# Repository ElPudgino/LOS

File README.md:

# Система мониторинга аэрационной ЛОС

Проект направлен на создание прототипа системы мониторинга аэрационной станции биологической очистки сточных вод для загородного дома. Система должна контролировать поток воды в эрлифтах и давление в воздухных магистралях, передавать показания из станции в дом по радиоканалу, сохранять историю и заранее предупреждать о неполадках.

Главная задача — обнаруживать засоры эрлифтов, снижение производительности компрессоров и нарушение режимов работы до переполнения камер и ухудшения качества очистки. Проектная цель предусматривает автономный влагозащищённый измерительный блок в станции и домашний блок приёма, хранения и анализа данных.

Основное описание целей, требований и существующих аналогов: [scs-project-docs/project.md](scs-project-docs/project.md) и [PDF](scs-project-docs/project.pdf).

## Репозитории

### Документация

| Репозиторий | Назначение |
| --- | --- |
| [scs-project-docs](scs-project-docs/) | Цели и требования проекта, описание системы, обзор аналогов, схемы и проектное предложение. |
| [scs-docs](scs-docs/) | Справочные материалы: документация на микросхемы, датчики и модули, распиновки и другие технические материалы. |

### Прошивки и программное обеспечение

| Репозиторий | Назначение |
| --- | --- |
| [scs-ch32v003-sensor](scs-ch32v003-sensor/) | Bare-metal прошивка CH32V003 для ёмкостного датчика воды в эрлифте: RC-измерения, оценка изменчивости сигнала, энергосбережение и UART. |
| [scs-transmitter-fw-v1](scs-transmitter-fw-v1/) | Прошивка передатчика на Arduino Nano и CC1101: опрос трёх датчиков по UART, проверка CRC и передача измерений и ошибок по радиоканалу. |
| [scs-receiver-fw-v1](scs-receiver-fw-v1/) | Прошивка домашнего приёмника на Arduino Nano и CC1101: приём радиопакетов и выдача телеметрии на компьютер через USB-UART. |
| [scs-frontend](scs-frontend/) | Локальный сервис на Python/FastAPI и веб-интерфейс для сбора телеметрии, хранения истории в SQLite, графиков, статистики и диагностики. |
| [scs-air-valve-arduino](scs-air-valve-arduino/) | Прошивка контроллера воздушного клапана модели септика: управление сервоприводом по состоянию поплавкового датчика. |

### Платы, конструкции и стендовое оборудование

| Репозиторий | Назначение |
| --- | --- |
| [scs-water-sensor-ch32v003](scs-water-sensor-ch32v003/) | Схема и гибкая печатная плата ёмкостного датчика на CH32V003J4M6 с измерительной RC-цепью и интерфейсом UART/SWIO. |
| [scs-transmitter-pcb-v1](scs-transmitter-pcb-v1/) | Плата передатчика: Arduino Nano, CC1101, согласование уровней и подключение трёх датчиков. |
| [scs-receiver-pcb-v1](scs-receiver-pcb-v1/) | Плата приёмника: Arduino Nano, CC1101 и согласователь логических уровней. |
| [scs-air-valve-pcb](scs-air-valve-pcb/) | Плата контроллера воздушного клапана на Arduino Nano с подключением сервопривода, поплавка и питания. |
| [scs-stand-ps](scs-stand-ps/) | Изолированный трансформаторный блок питания стенда: схема, печатная плата и файлы для её изготовления. |
| [scs-3d-models](scs-3d-models/) | Корпуса, крепления и механические узлы датчиков и стенда; исходные 3D-модели и файлы для печати. |

### Инструменты разработки

| Репозиторий | Назначение |
| --- | --- |
| [scs-arduino-ch32v003-swio](scs-arduino-ch32v003-swio/) | Варианты адаптера UART–SWIO на ATmega328P для прошивки и отладки CH32V003 через minichlink. |
| [minichlink](minichlink/) | Сторонний инструмент для прошивки и отладки CH32V003 через WCH-LinkE, включая GDB-сервер и поддержку Ardulink. |
| [arduino-offline](arduino-offline/) | Локальный набор Arduino CLI, Arduino AVR Core и компилятора для автономной сборки Arduino-прошивок. |

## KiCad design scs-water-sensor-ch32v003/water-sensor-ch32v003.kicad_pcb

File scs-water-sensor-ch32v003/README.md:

# Схема и плата для датчика потока воды

Датчик построен на базе микроконтроллера CH32V003. Прошивка в папке ../../software/ch32v003-sensor.

Печатная плата выполнена на гибкой полиимидной основе толщиной 0.1мм.

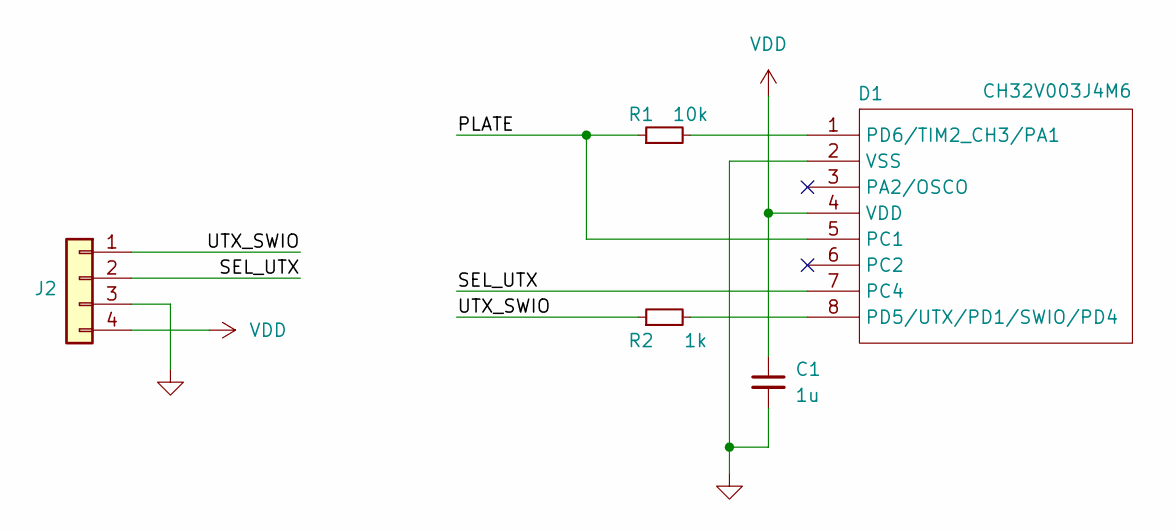
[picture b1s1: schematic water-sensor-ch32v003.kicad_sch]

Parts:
C1: 1u; C_0805_2012Metric_Pad1.18x1.45mm_HandSolder
D1: CH32V003J4M6; SOIC-8_3.9x4.9mm_P1.27mm
J2: Conn_01x04; CONN4
R1: 10k; R_0805_2012Metric_Pad1.20x1.40mm_HandSolder
R2: 1k; R_0805_2012Metric_Pad1.20x1.40mm_HandSolder

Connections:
/PLATE: D1.5 (PC1), R1.1
/SEL_UTX: D1.7 (PC4), J2.2
/UTX_SWIO: J2.1, R2.1
GND: C1.2, D1.2 (VSS), J2.3
unnamed: D1.8 (PD5/UTX/PD1/SWIO/PD4), R2.2
unnamed: D1.1 (PD6/TIM2_CH3/PA1), R1.2
VDD: C1.1, D1.4 (VDD), J2.4

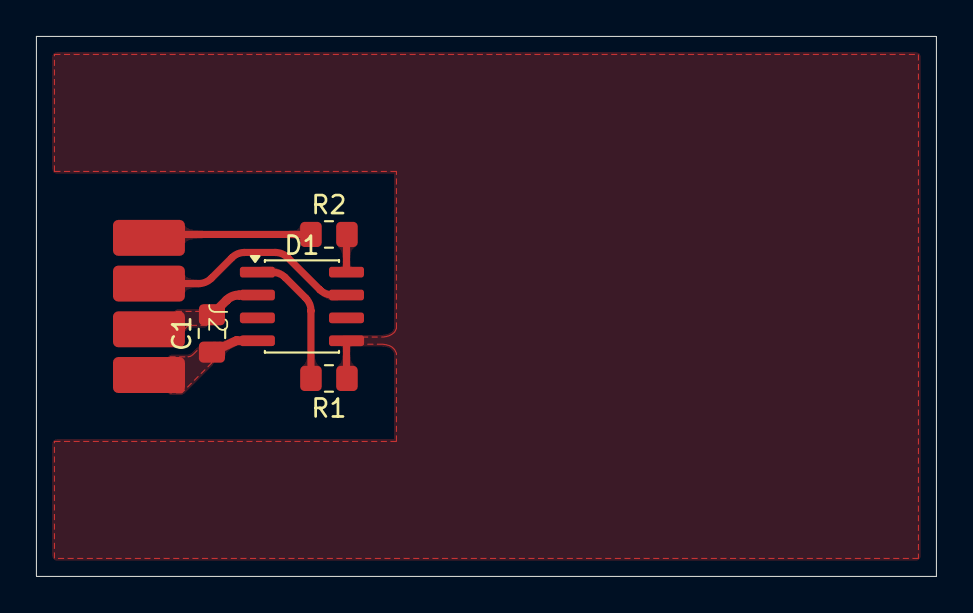
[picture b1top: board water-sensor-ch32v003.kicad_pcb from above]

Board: 2 copper layers, 50.0 x 30.0 mm, 5 parts (0 on the bottom side), 7 nets.

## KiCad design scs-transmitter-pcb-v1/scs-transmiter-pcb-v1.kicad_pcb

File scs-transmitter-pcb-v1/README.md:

# Печатная плата передатчика телеметрии

Плата измерительного блока системы мониторинга на Arduino Nano и радиомодуле CC1101. Предусмотрены согласование логических уровней, подключение трёх датчиков, транзисторные цепи запросов и объединение их линий UART TX.

Проект выполнен в KiCad и предназначен для работы с прошивкой [scs-transmitter-fw-v1](../scs-transmitter-fw-v1/).

- [scs-transmiter-pcb-v1.pdf](scs-transmiter-pcb-v1.pdf) — принципиальная схема в PDF.
- `scs-transmiter-pcb-v1.kicad_sch` и `scs-transmiter-pcb-v1.kicad_pcb` — схема и топология платы.
- `gerber/` — Gerber-файлы и сверловка для изготовления.
- `cnc/` — конфигурация и файлы для фрезеровки платы.

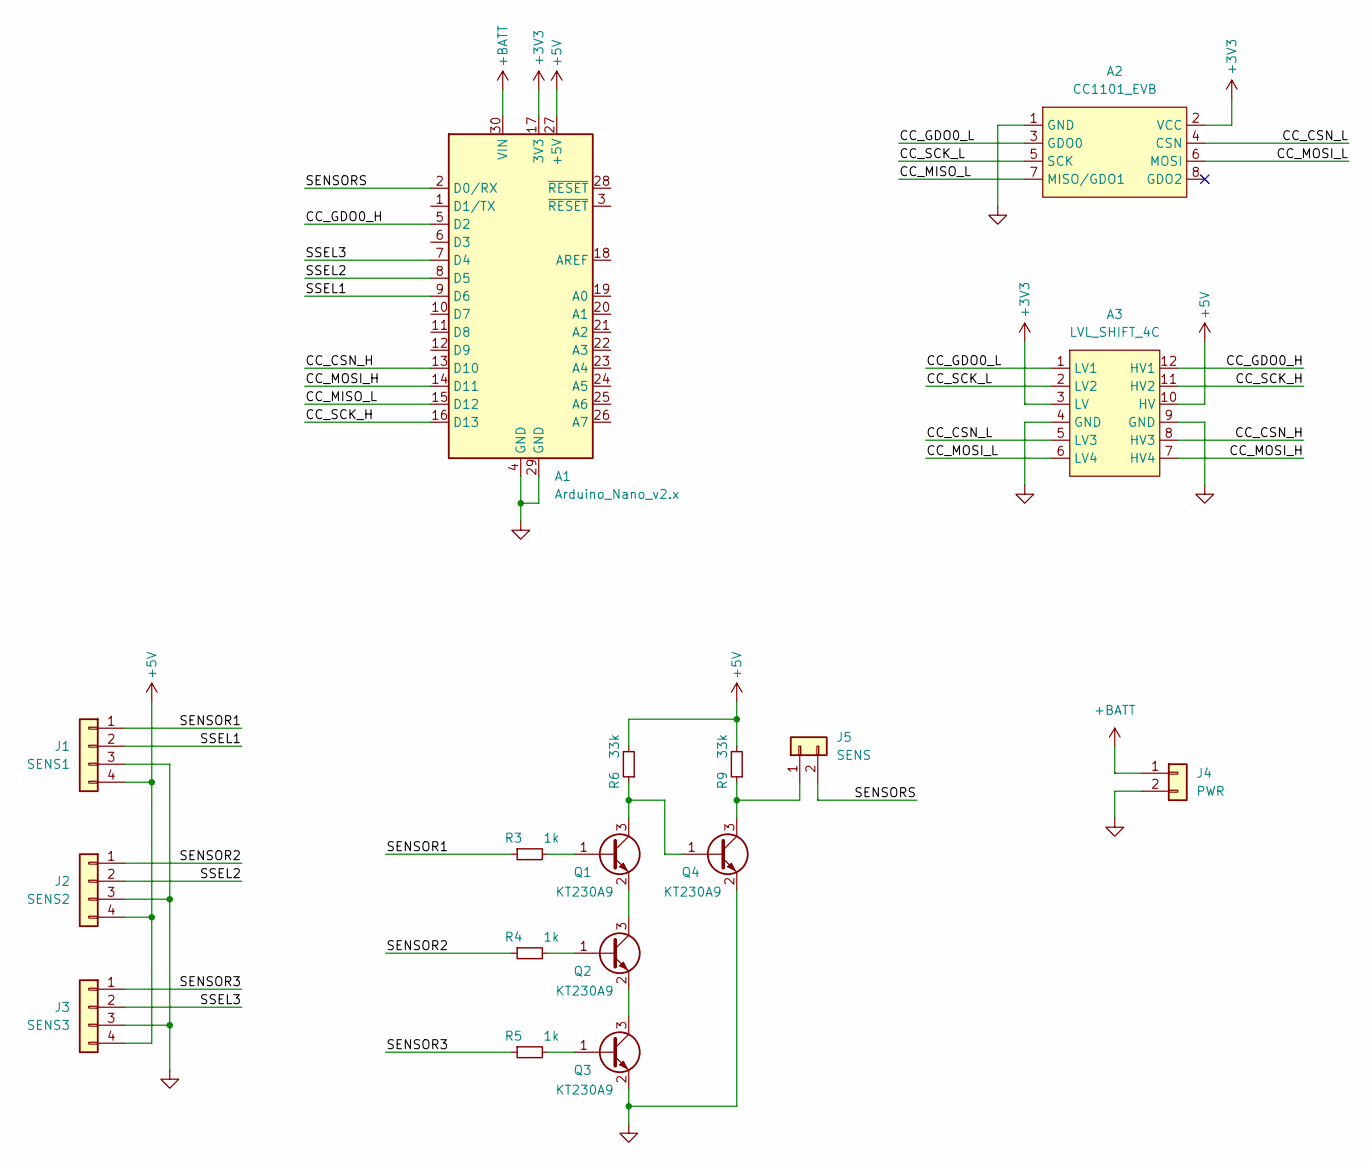
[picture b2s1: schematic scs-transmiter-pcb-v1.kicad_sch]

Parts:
A1: Arduino_Nano_v2.x; Arduino_Nano
A2: CC1101_EVB
A3: LVL_SHIFT_4C
J1: SENS1; PinHeader_1x04_P2.54mm_Vertical
J2: SENS2; PinHeader_1x04_P2.54mm_Vertical
J3: SENS3; PinHeader_1x04_P2.54mm_Vertical
J4: PWR; PinHeader_1x02_P2.54mm_Vertical
J5: SENS; PinHeader_1x02_P2.54mm_Vertical
Q1, Q2, Q3, Q4: КТ230А9; SOT-23
R3, R4, R5: 1k; R_0805_2012Metric_Pad1.20x1.40mm_HandSolder
R6, R9: 33k; R_0805_2012Metric_Pad1.20x1.40mm_HandSolder

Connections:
+3V3: A1.17 (3V3), A2.2 (VCC), A3.3 (LV)
+5V: A1.27 (+5V), A3.10 (HV), J1.4, J2.4, J3.4, R6.2, R9.2
+BATT: A1.30 (VIN), J4.1
/CC_CSN_H: A1.13 (D10), A3.8 (HV3)
/CC_CSN_L: A2.4 (CSN), A3.5 (LV3)
/CC_GDO0_H: A1.5 (D2), A3.12 (HV1)
/CC_GDO0_L: A2.3 (GDO0), A3.1 (LV1)
/CC_MISO_L: A1.15 (D12), A2.7 (MISO/GDO1)
/CC_MOSI_H: A1.14 (D11), A3.7 (HV4)
/CC_MOSI_L: A2.6 (MOSI), A3.6 (LV4)
/CC_SCK_H: A1.16 (D13), A3.11 (HV2)
/CC_SCK_L: A2.5 (SCK), A3.2 (LV2)
/SENSOR1: J1.1, R3.1
/SENSOR2: J2.1, R4.1
/SENSOR3: J3.1, R5.1
/SENSORS: A1.2 (D0/RX), J5.2
/SSEL1: A1.9 (D6), J1.2
/SSEL2: A1.8 (D5), J2.2
/SSEL3: A1.7 (D4), J3.2
GND: A1.4 (GND), A1.29 (GND), A2.1 (GND), A3.4 (GND), A3.9 (GND), J1.3, J2.3, J3.3, J4.2, Q3.2 (E), Q4.2 (E)
unnamed: J5.1, Q4.3 (C), R9.1
unnamed: Q1.1 (B), R3.2
unnamed: Q1.3 (C), Q4.1 (B), R6.1
unnamed: Q1.2 (E), Q2.3 (C)
unnamed: Q2.1 (B), R4.2
unnamed: Q2.2 (E), Q3.3 (C)
unnamed: Q3.1 (B), R5.2

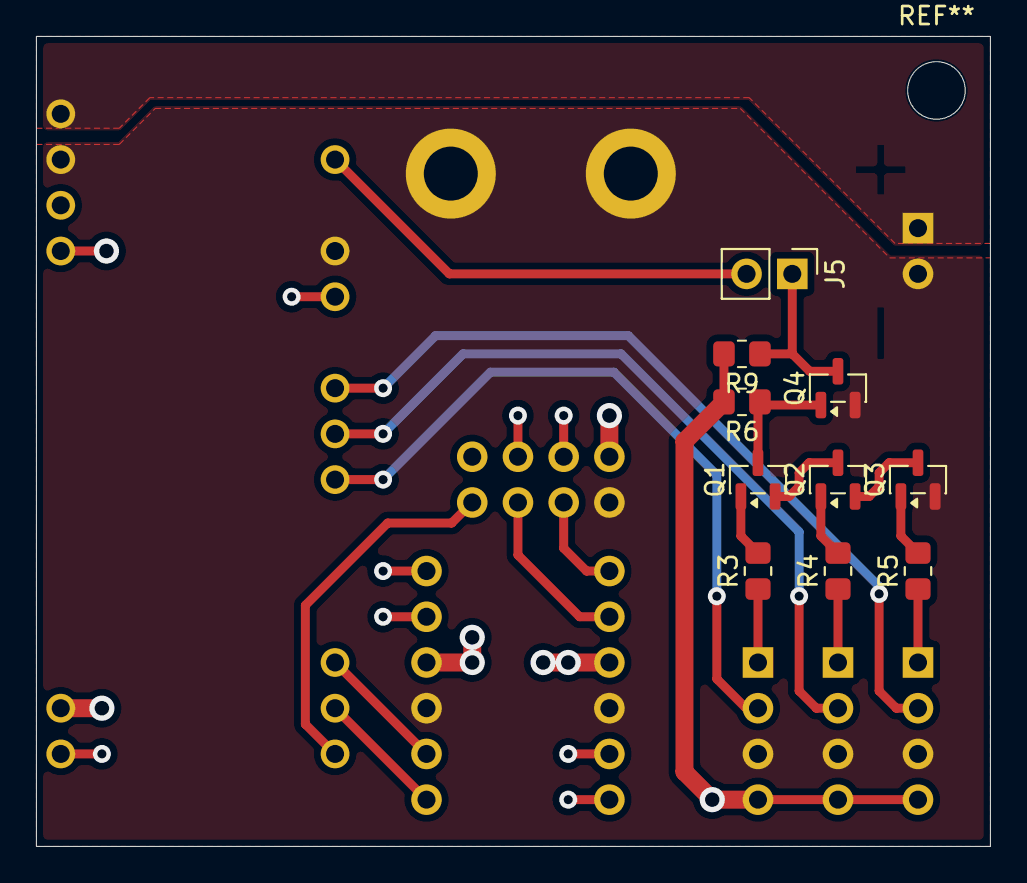
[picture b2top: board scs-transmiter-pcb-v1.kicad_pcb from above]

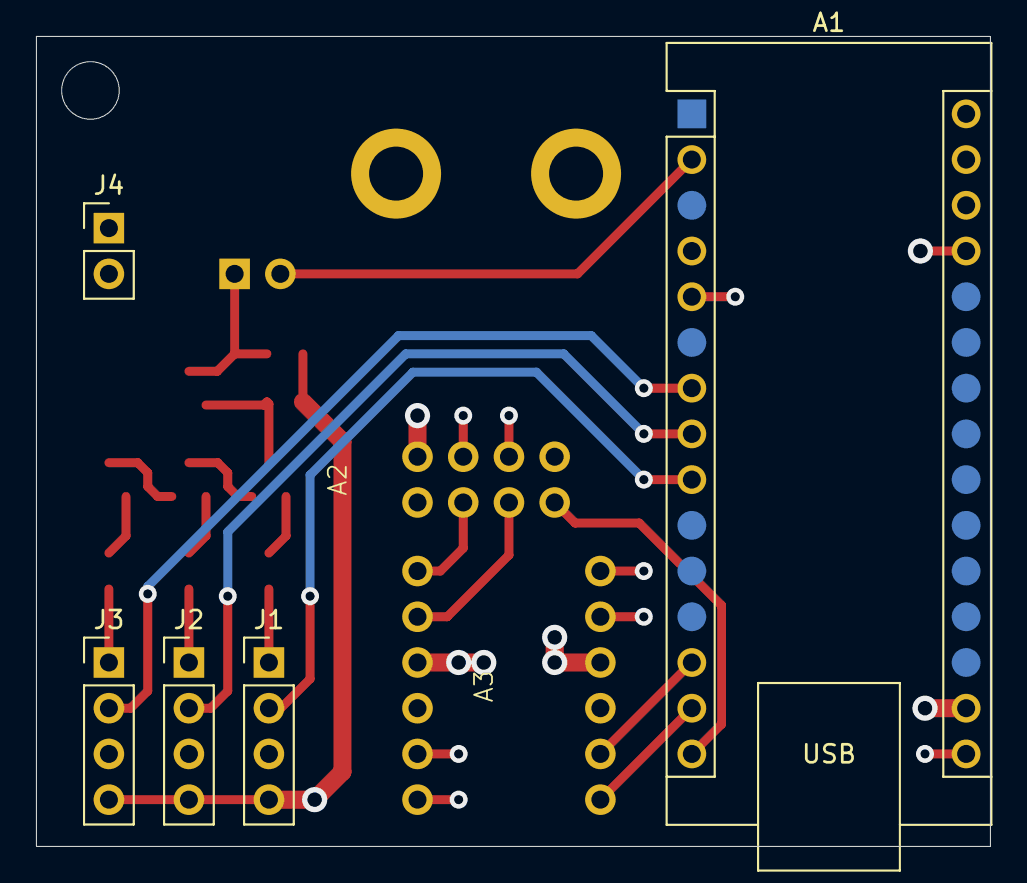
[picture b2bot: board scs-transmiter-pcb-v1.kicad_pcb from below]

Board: 2 copper layers, 53.0 x 45.0 mm, 17 parts (7 on the bottom side), 27 nets.

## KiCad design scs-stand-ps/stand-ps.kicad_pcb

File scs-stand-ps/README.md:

# Трансформаторный источник питания для стенда

Для обеспечения электробезопасности все электрические элементы стенда запитываются от изолированного трансформаторного БП. В этой папке проект печатной платы БП. Плата изготавливалась на станке ЧПУ, конфиг для `pcb2gcode` находится в папке `mill`.

Основа - трансформатор ТП-1201 с номинальным напряжением на вторичной обмотке 6В.

Схема в файле [stand-ps.pdf](stand-ps.pdf).

Форма выходного напряжения при нагрузке 1А:

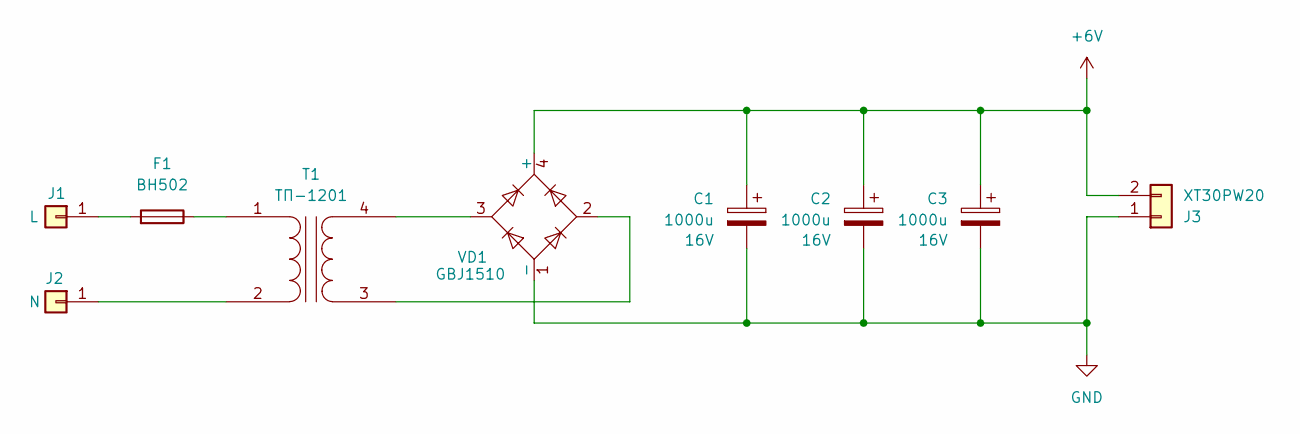
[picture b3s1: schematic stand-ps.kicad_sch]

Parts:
C1, C2, C3: 1000u; C_Radial_D10.0mm_H16.0mm_P5.00mm; Voltage 16V
F1: BH502
J1: L; TH3
J2: N; TH3
J3: XT30PW20; AMASS_XT30PW-M_1x02_P2.50mm_Horizontal
T1: ТП-1201; TP-1201
VD1: GBJ1510; Diode_Bridge_32.0x5.6x17.0mm_P10.0mm_P7.5mm

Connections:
+6V: C1.1, C2.1, C3.1, J3.2, VD1.4 (+)
GND: C1.2, C2.2, C3.2, J3.1, VD1.1 (-)
unnamed: F1.2, J1.1 (Pin_1_1)
unnamed: J2.1 (Pin_1_1), T1.2 (AB)
unnamed: F1.1, T1.1 (AA)
unnamed: T1.3 (SA), VD1.2
unnamed: T1.4 (SB), VD1.3

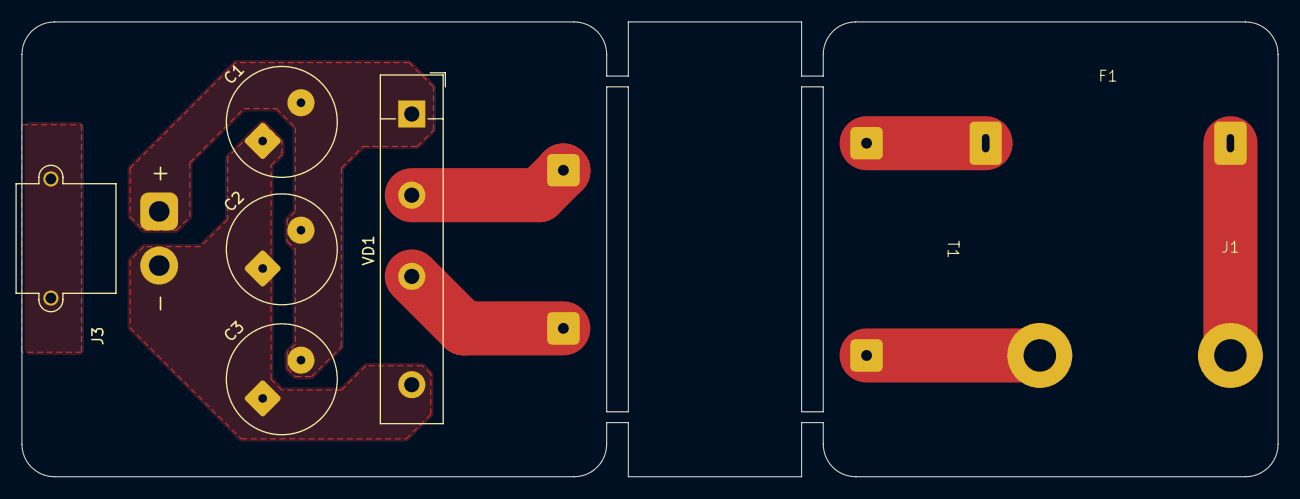
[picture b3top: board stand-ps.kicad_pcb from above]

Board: 2 copper layers, 116.0 x 42.0 mm, 9 parts (0 on the bottom side), 7 nets.

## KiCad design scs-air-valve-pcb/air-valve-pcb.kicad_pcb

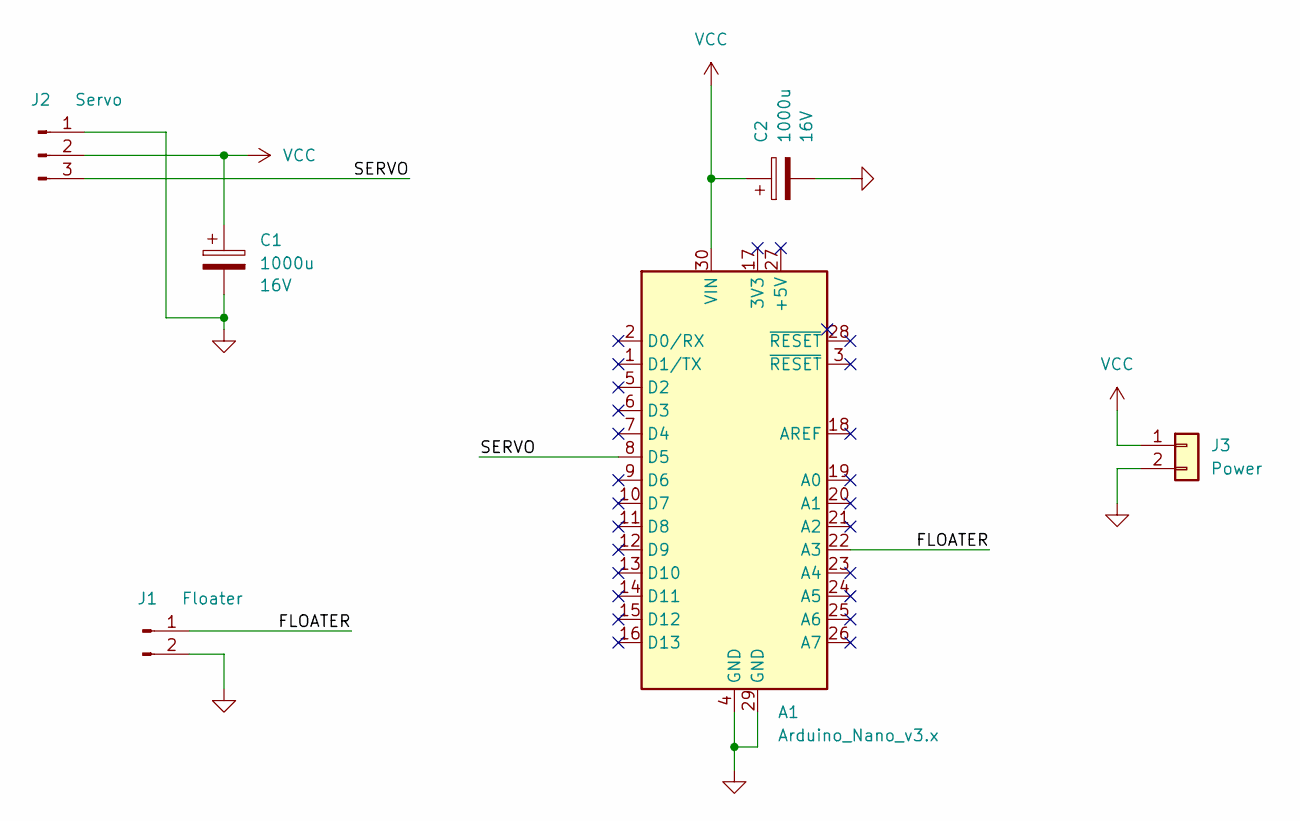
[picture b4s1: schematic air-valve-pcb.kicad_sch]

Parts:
A1: Arduino_Nano_v3.x; Arduino_Nano
C1, C2: 1000u; C_Radial_D10.0mm_H16.0mm_P5.00mm; Voltage 16V
J1: Floater; PinHeader_1x02_P2.54mm_Vertical
J2: Servo; PinHeader_1x03_P2.54mm_Vertical
J3: Power; AMASS_XT30PW-M_1x02_P2.50mm_Horizontal

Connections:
/FLOATER: A1.22 (A3), J1.1
/SERVO: A1.8 (D5), J2.3
GND: A1.4 (GND), A1.29 (GND), C1.2, C2.2, J1.2, J2.1, J3.2
VCC: A1.30 (VIN), C1.1, C2.1, J2.2, J3.1

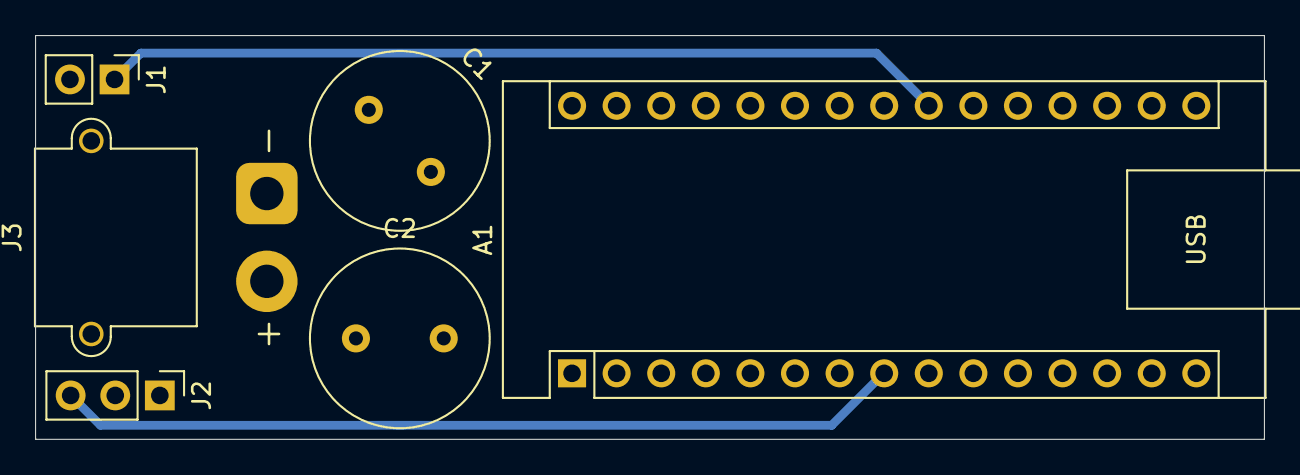
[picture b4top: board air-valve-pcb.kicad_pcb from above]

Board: 2 copper layers, 70.0 x 23.0 mm, 6 parts (0 on the bottom side), 4 nets.

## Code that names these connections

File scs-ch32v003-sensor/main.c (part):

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#error "SAMPLES must be 1..131"
#endif

/* SOP8, full TIM2 remap: CH1=PC1 (B, pin 5), CH3=PD6 (A, pin 1).
 * PA1 shares pin 1: leave it floating; keep the external oscillator off. */
#define A_PIN (1u << 6)
#define B_PIN (1u << 1)
#define A_CFG_SHIFT 24u
#define B_CFG_SHIFT 4u

#define SELECT_PIN (1u << 4)        /* PC4, SOP8 pin 7 */
#define SELECT_CFG_SHIFT 16u

#define GPIO_PULL    0x8u           /* Input pull-up/down; OUTDR selects direction */
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    PFIC_SCTLR |= WFITOWFE;
    PWR_AWUCSR |= AWU_ENABLE;

    /* The synthetic event may have consumed a real PC4 event too. Its
     * sticky interrupt flag survives: do not sleep again if it is pending.
     * An edge after this check supplies the final WFE's wake event. */
    if (!(EXTI_INTFR & REQUEST_EVENT))
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
static uint32_t uart_init_if_selected(void)
{
    /* PC4 pull-up: open = UART, grounded = keep SWIO untouched. */
    GPIOC_BSHR = SELECT_PIN;
    GPIOC_CFGLR = (GPIOC_CFGLR & ~(0xfu << SELECT_CFG_SHIFT))
                 | (GPIO_PULL << SELECT_CFG_SHIFT);
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    USART_CTLR3 = 0;               /* No flow control, DMA or special modes */
    USART_BRR = 2500u;             /* 24 MHz / 9600 */

    /* PD1, PD4 and PD5 share SOP8 pin 8: only PD5 may drive it. */
    GPIOD_CFGLR = (GPIOD_CFGLR & ~((0xfu << 4) | (0xfu << 16)))
                 | (GPIO_FLOAT << 4) | (GPIO_FLOAT << 16);

    /* SWCFG=100 disables SWIO; USART1_RM[21,2]=00 selects TX on PD5.
     * Preserve TIM2 full remap and all unrelated fields. */
    AFIO_PCFR1 = (AFIO_PCFR1 & ~((7u << 24) | (1u << 21) | (1u << 2)))
                 | (4u << 24);
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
